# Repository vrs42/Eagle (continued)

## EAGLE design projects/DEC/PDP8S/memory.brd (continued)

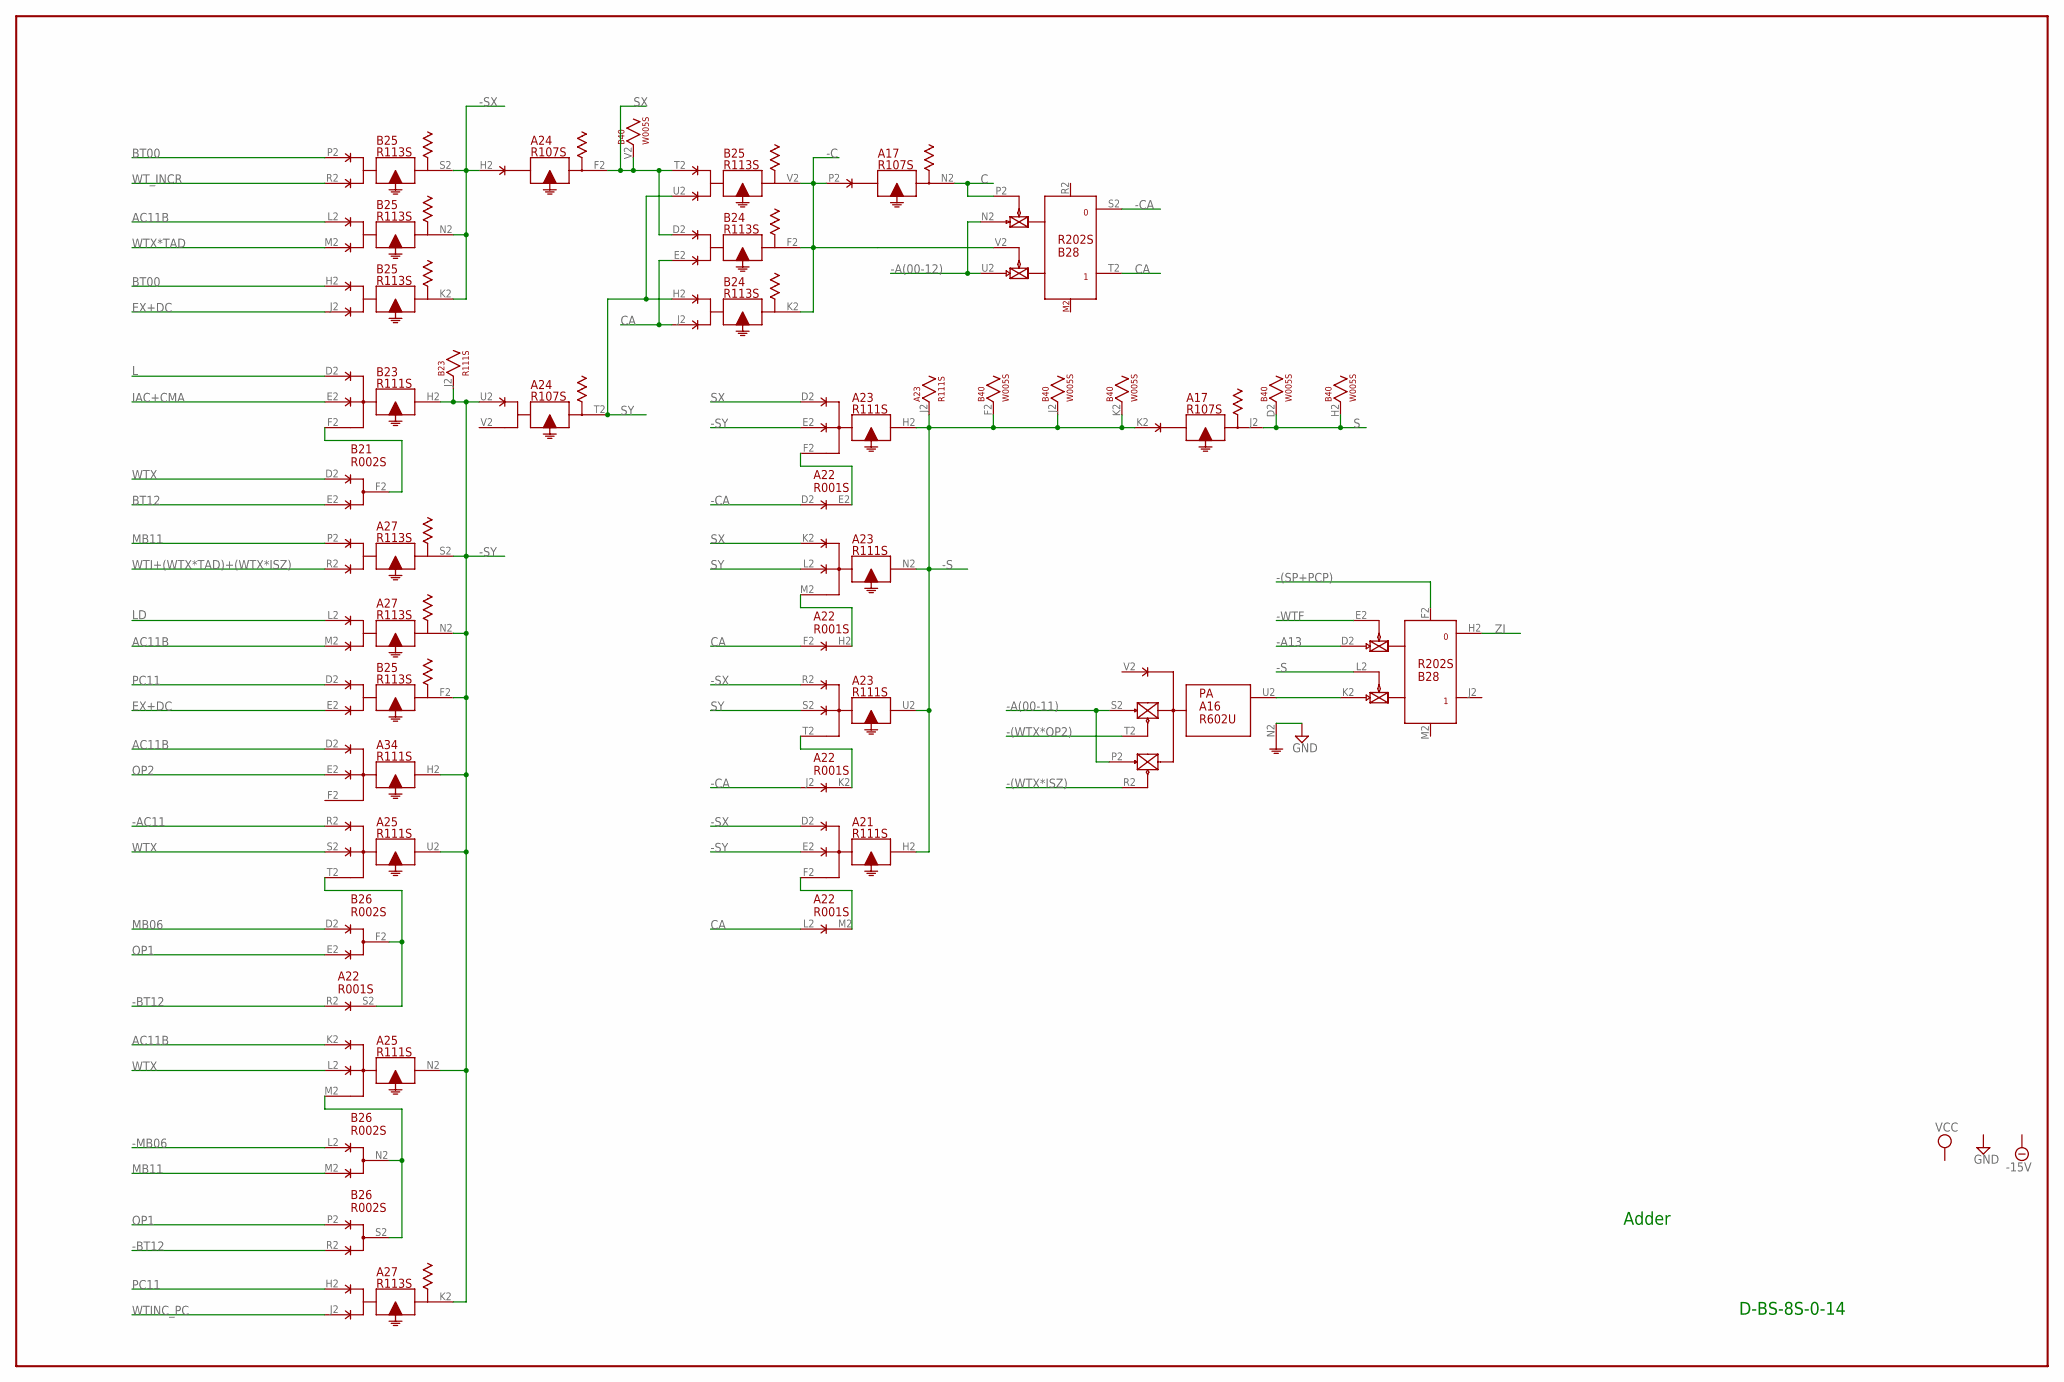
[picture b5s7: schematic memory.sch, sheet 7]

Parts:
A16: R602U; H807S
A17, A24: R107S; H807S
A21, A23, A25, A34: R111S; H807S
A22: R001S; H807S
A27: R113S; H807S
B21, B26: R002S; H807S
B23: R111S; H807S
B24, B25: R113S; H807S
B28: R202S; H807S
B40: W005S; H807S

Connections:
-15V: A16.B2 (-15V), A17.B2 (-15V), A21.B2 (-15V), A22.B2 (-15V), A23.B2 (-15V), A24.B2 (-15V), A25.B2 (-15V), A27.B2 (-15V), A34.B2 (-15V), B21.B2 (-15V), B23.B2 (-15V), B24.B2 (-15V), B25.B2 (-15V), B26.B2 (-15V), B28.B2 (-15V), B40.B2 (-15V); also elsewhere on the board
-(SP+PCP): B28.F2 (RESET); also elsewhere on the board
-(WTX*ISZ): A16.R2 (F); also elsewhere on the board
-(WTX*OP2): A16.T2 (J); also elsewhere on the board
-A13: B28.D2 (PU0); also elsewhere on the board
-A(00-11): A16.P2 (E), A16.S2 (H); also elsewhere on the board
-A(00-12): B28.N2 (PU0), B28.U2 (PU1); also elsewhere on the board
-AC11: A25.R2; also elsewhere on the board
-BT12: A22.R2 (D), B26.R2 (E); also elsewhere on the board
-C: A17.P2, B24.F2, B24.K2, B25.V2, B28.V2 (EN1)
-CA: A22.D2 (D), A22.J2 (D), B28.S2 (0)
-MB06: B26.L2 (D); also elsewhere on the board
-S: A17.K2, A21.H2, A23.H2, A23.J2, A23.N2, A23.U2, B28.L2 (EN1), B40.F2, B40.J2, B40.K2
-SX: A21.D2, A23.R2, A24.H2, B25.K2, B25.N2, B25.S2
-SY: A21.E2, A23.E2, A24.U2, A25.N2, A25.U2, A27.K2, A27.N2, A27.S2, A34.H2, B23.H2, B23.J2, B25.F2
-WTF: B28.E2 (EN0); also elsewhere on the board
AC11B: A25.K2, A27.M2, A34.D2, B25.L2; also elsewhere on the board
BT00: B25.H2, B25.P2; also elsewhere on the board
BT12: B21.E2 (E); also elsewhere on the board
C: A17.N2, B28.P2 (EN0)
CA: A22.F2 (D), A22.L2 (D), B24.E2, B24.J2, B28.T2 (1)
EX+DC: B25.E2, B25.J2; also elsewhere on the board
GND: A16.N2 (C), A17.C2 (GND), A21.C2 (GND), A22.C2 (GND), A23.C2 (GND), A24.C2 (GND), A25.C2 (GND), A27.C2 (GND), A34.C2 (GND), B21.C2 (GND), B23.C2 (GND), B24.C2 (GND), B25.C2 (GND), B26.C2 (GND), B28.C2 (GND), B40.C2 (GND); also elsewhere on the board
IAC+CMA: B23.E2; also elsewhere on the board
L: B23.D2; also elsewhere on the board
LD: A27.L2; also elsewhere on the board
MB06: B26.D2 (D); also elsewhere on the board
MB11: A27.P2, B26.M2 (E); also elsewhere on the board
unnamed: B21.F2 (F), B23.F2
unnamed: A16.U2 (K), B28.K2 (PU1)
unnamed: A22.S2 (E), A25.T2, B26.F2 (F)
unnamed: A22.E2 (E), A23.F2
unnamed: A25.M2, B26.N2 (F), B26.S2 (F)
unnamed: A22.H2 (E), A23.M2
unnamed: A22.K2 (E), A23.T2
unnamed: A21.F2, A22.M2 (E)
OP1: B26.E2 (E), B26.P2 (D); also elsewhere on the board
OP2: A34.E2; also elsewhere on the board
PC11: A27.H2, B25.D2; also elsewhere on the board
S: A17.J2, B40.D2, B40.H2; also elsewhere on the board
SX: A23.D2, A23.K2, A24.F2, B24.D2, B25.T2, B40.V2
SY: A23.L2, A23.S2, A24.T2, B24.H2, B25.U2
VCC: A16.A2 (VCC), A17.A2 (VCC), A21.A2 (VCC), A22.A2 (VCC), A23.A2 (VCC), A24.A2 (VCC), A25.A2 (VCC), A27.A2 (VCC), A34.A2 (VCC), B21.A2 (VCC), B23.A2 (VCC), B24.A2 (VCC), B25.A2 (VCC), B26.A2 (VCC), B28.A2 (VCC), B40.A2 (VCC); also elsewhere on the board
WTI+(WTX*TAD)+(WTX*ISZ): A27.R2; also elsewhere on the board
WTINC_PC: A27.J2; also elsewhere on the board
WTX: A25.L2, A25.S2, B21.D2 (D); also elsewhere on the board
WTX*TAD: B25.M2; also elsewhere on the board
WT_INCR: B25.R2; also elsewhere on the board
ZI: B28.H2 (0); also elsewhere on the board

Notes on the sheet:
D-BS-8S-0-14
Adder

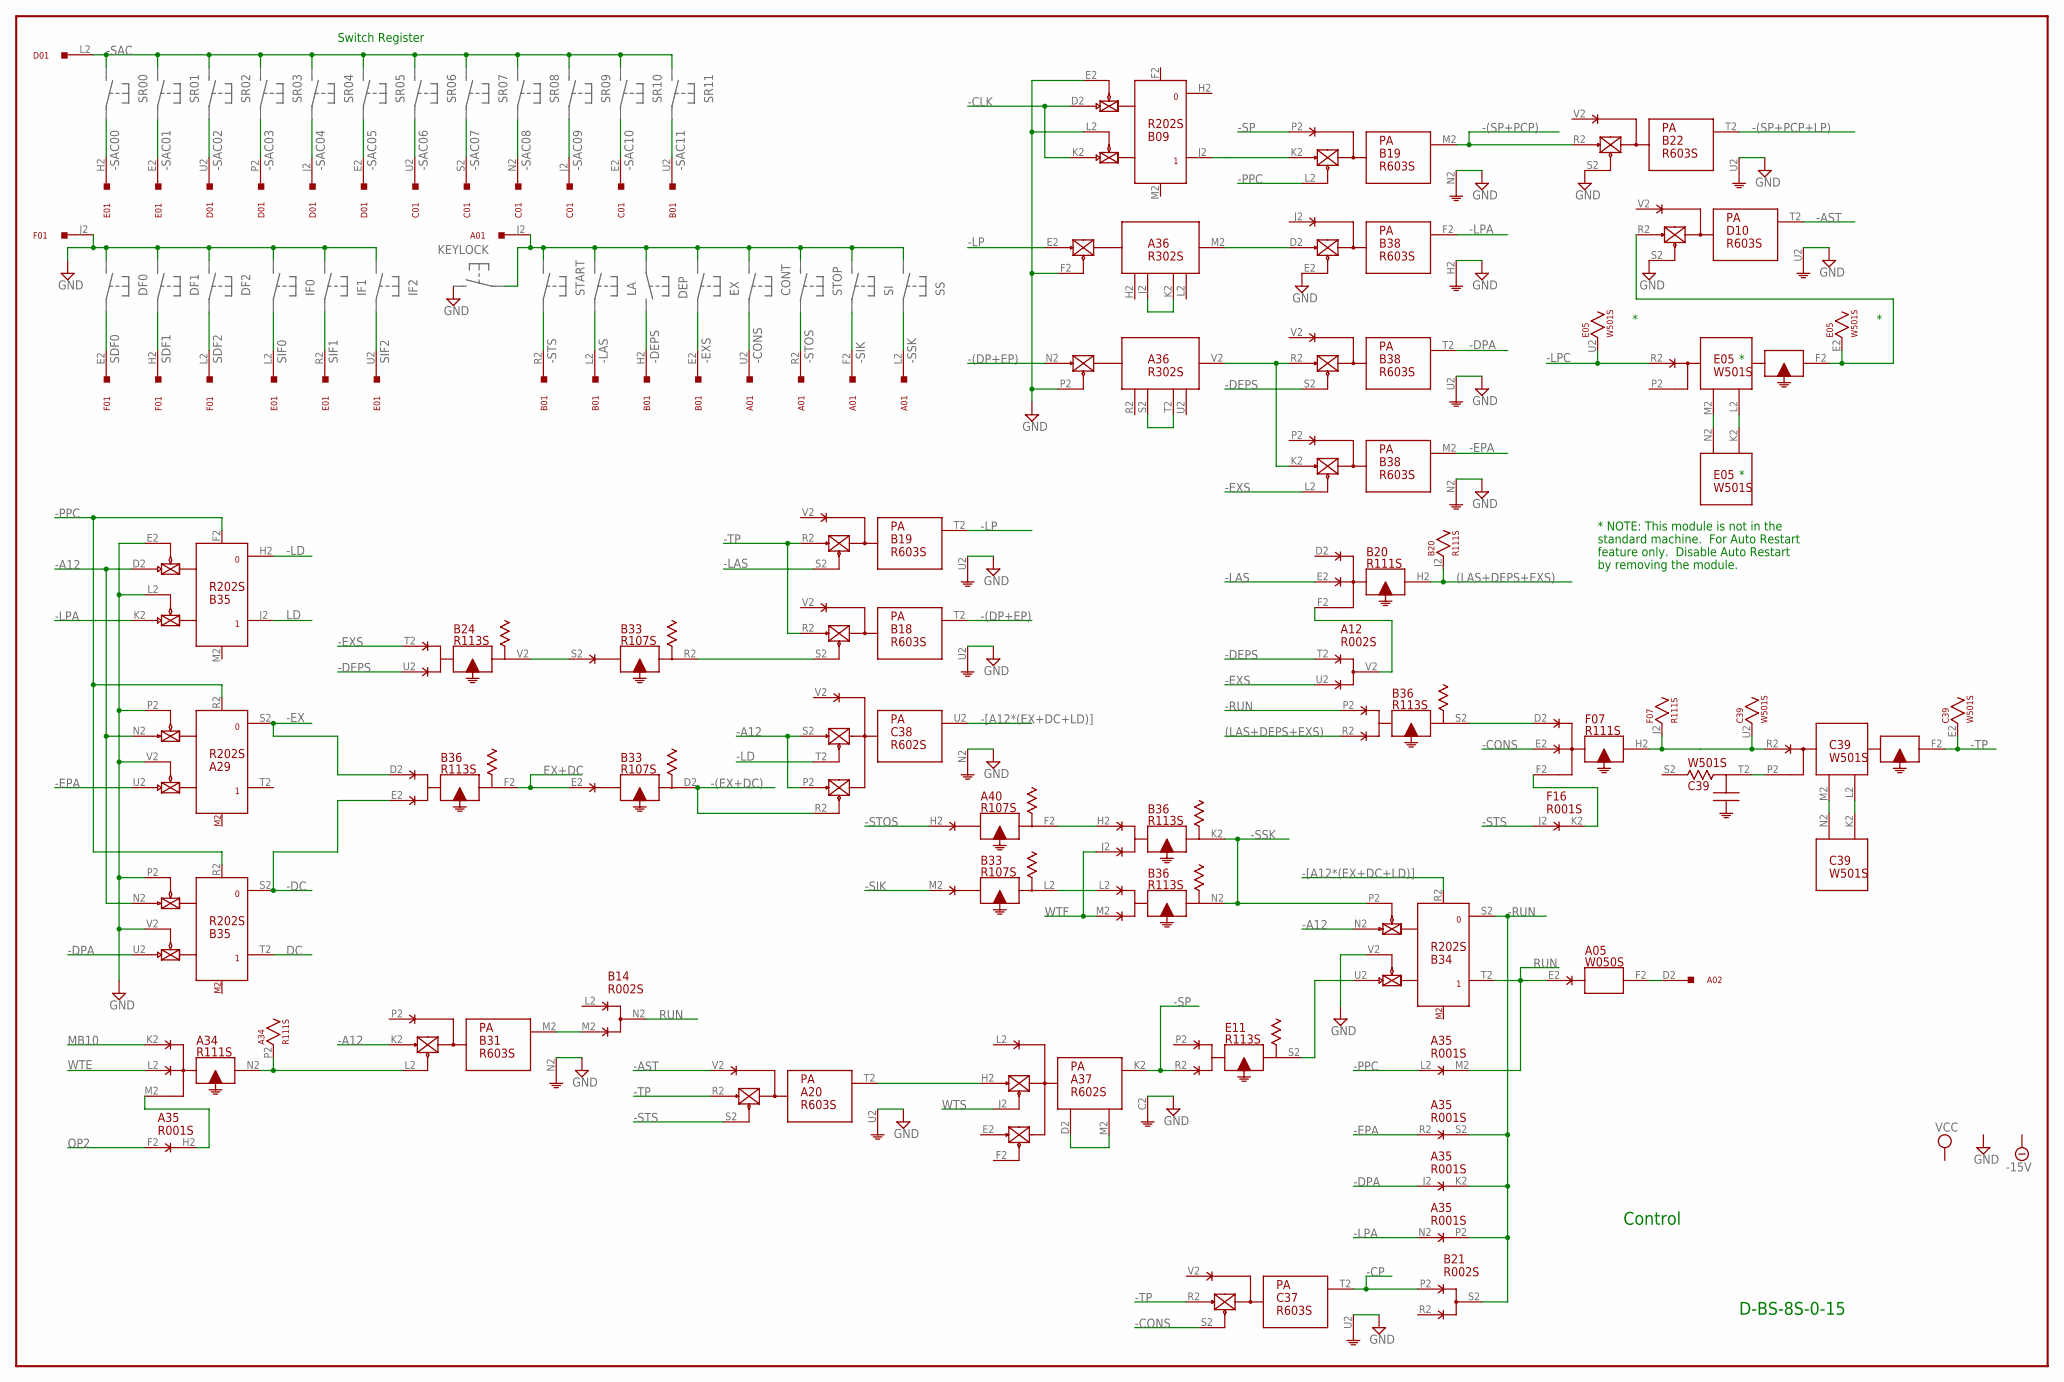
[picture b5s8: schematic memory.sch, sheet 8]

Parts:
A01, A02: W023S; H807S
A05: W050S; H807S
A12: R002S; H807S
A20: R603S; H807S
A29: R202S; H807S
A34: R111S; H807S
A35: R001S; H807S
A36: R302S; H807S
A37: R602S; H807S
A40: R107S; H807S
B01: W023S; H807S
B09, B34, B35: R202S; H807S
B14, B21: R002S; H807S
B18, B19, B22, B31, B38: R603S; H807S
B20: R111S; H807S
B24, B36: R113S; H807S
B33: R107S; H807S
C01: W023S; H807S
C37: R603S; H807S
C38: R602S; H807S
C39: W501S; H807S
D01: W023S; H807S
D10: R603S; H807S
E01: W023S; H807S
E05: W501S; H807S
E11: R113S; H807S
F01: W023S; H807S
F07: R111S; H807S
F16: R001S; H807S

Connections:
(LAS+DEPS+EXS): B20.H2, B20.J2, B36.R2
-15V: A05.B2 (-15V), A12.B2 (-15V), A20.B2 (-15V), A29.B2 (-15V), A34.B2 (-15V), A35.B2 (-15V), A36.B2 (-15V), A37.B2 (-15V), A40.B2 (-15V), B09.B2 (-15V), B14.B2 (-15V), B18.B2 (-15V), B19.B2 (-15V), B20.B2 (-15V), B21.B2 (-15V), B22.B2 (-15V), B24.B2 (-15V), B31.B2 (-15V), B33.B2 (-15V), B34.B2 (-15V), B35.B2 (-15V), B36.B2 (-15V), B38.B2 (-15V), C37.B2 (-15V), C38.B2 (-15V), C39.B2 (-15V), D10.B2 (-15V), E05.B2 (-15V), E11.B2 (-15V), F07.B2 (-15V), F16.B2 (-15V); also elsewhere on the board
-(DP+EP): A36.N2 (E), B18.T2 (O); also elsewhere on the board
-(EX+DC): B33.D2, C38.R2 (F); also elsewhere on the board
-(SP+PCP): B19.M2 (O), B22.R2 (PU0); also elsewhere on the board
-(SP+PCP+LP): B22.T2 (O); also elsewhere on the board
-A12: A29.N2 (PU0), B31.K2 (PU0), B34.N2 (PU0), B35.D2 (PU0), B35.N2 (PU0), C38.P2 (E), C38.S2 (H); also elsewhere on the board
-AST: A20.V2, D10.T2 (O)
-CLK: B09.D2 (PU0), B09.K2 (PU1); also elsewhere on the board
-CONS: A01.U2, C37.S2 (EN0), F07.E2
-CP: B21.P2 (D), C37.T2 (O)
-DC: B35.S2 (0), B36.E2; also elsewhere on the board
-DEPS: A12.T2 (D), B01.H2, B24.U2, B38.S2 (EN0)
-DPA: A35.J2 (D), B35.U2 (PU1), B38.T2 (O); also elsewhere on the board
-EPA: A29.U2 (PU1), A35.R2 (D), B38.M2 (O); also elsewhere on the board
-EX: A29.S2 (0), B36.D2; also elsewhere on the board
-EXS: A12.U2 (E), B01.E2, B24.T2, B38.L2 (EN0)
-LAS: B01.L2, B19.S2 (EN0), B20.E2
-LD: B35.H2 (0), C38.T2 (J); also elsewhere on the board
-LP: A36.E2 (E), B19.T2 (O); also elsewhere on the board
-LPA: A35.N2 (D), B35.K2 (PU1), B38.F2 (O); also elsewhere on the board
-LPC: E05.R2 (R), E05.U2; also elsewhere on the board
-PPC: A29.R2 (RESET), A35.L2 (D), B19.L2 (EN0), B35.F2 (RESET), B35.R2 (RESET); also elsewhere on the board
-RUN: A35.K2 (E), A35.P2 (E), A35.S2 (E), B21.S2 (F), B34.S2 (0), B36.P2; also elsewhere on the board
-SAC: D01.L2; also elsewhere on the board
-SAC00: E01.H2; also elsewhere on the board
-SAC01: E01.E2; also elsewhere on the board
-SAC02: D01.U2; also elsewhere on the board
-SAC03: D01.P2; also elsewhere on the board
-SAC04: D01.J2; also elsewhere on the board
-SAC05: D01.E2; also elsewhere on the board
-SAC06: C01.U2; also elsewhere on the board
-SAC07: C01.S2; also elsewhere on the board
-SAC08: C01.N2; also elsewhere on the board
-SAC09: C01.J2; also elsewhere on the board
-SAC10: C01.E2; also elsewhere on the board
-SAC11: B01.U2; also elsewhere on the board
-SIK: A01.F2, B33.M2
-SP: A37.K2 (K), B19.P2, E11.R2; also elsewhere on the board
-SSK: A01.L2, B34.P2 (EN0), B36.K2, B36.N2
-STOS: A01.R2, A40.H2
-STS: A20.S2 (EN0), B01.R2, F16.J2 (D)
-TP: A20.R2 (PU0), B18.R2 (PU0), B19.R2 (PU0), C37.R2 (PU0), C39.E2, C39.F2 (F)
-[A12*(EX+DC+LD)]: B34.R2 (RESET), C38.U2 (K); also elsewhere on the board
DC: B35.T2 (1); also elsewhere on the board
EX+DC: B33.E2, B36.F2; also elsewhere on the board
GND: A05.C2 (GND), A12.C2 (GND), A20.C2 (GND), A20.U2 (G), A29.C2 (GND), A29.P2 (EN0), A29.V2 (EN1), A34.C2 (GND), A35.C2 (GND), A36.C2 (GND), A36.F2 (F), A36.P2 (F), A37.C2 (GND), A40.C2 (GND), B09.C2 (GND), B09.E2 (EN0), B09.L2 (EN1), B14.C2 (GND), B18.C2 (GND), B18.U2 (G), B19.C2 (GND), B19.N2 (G), B19.U2 (G), B20.C2 (GND), B21.C2 (GND), B22.C2 (GND), B22.S2 (EN0), B22.U2 (G), B24.C2 (GND), B31.C2 (GND), B31.N2 (G), B33.C2 (GND), B34.C2 (GND), B34.V2 (EN1), B35.C2 (GND), B35.E2 (EN0), B35.L2 (EN1), B35.P2 (EN0), B35.V2 (EN1), B36.C2 (GND), B38.C2 (GND), B38.E2 (EN0), B38.H2 (G), B38.N2 (G), B38.U2 (G), C37.C2 (GND), C37.U2 (G), C38.N2 (C), C39.C2 (GND), C39.V2 (GND), D10.C2 (GND), D10.S2 (EN0), D10.U2 (G), E05.C2 (GND), E05.V2 (GND), E11.C2 (GND), F01.J2, F07.C2 (GND), F16.C2 (GND); also elsewhere on the board
KEYLOCK: A01.J2
LD: B35.J2 (1); also elsewhere on the board
MB10: A34.K2; also elsewhere on the board
unnamed: A34.M2, A35.H2 (E)
unnamed: A34.N2, A34.P2, B31.L2 (EN0)
unnamed: B14.M2 (E), B31.M2 (O)
unnamed: B24.V2, B33.S2
unnamed: B34.U2 (PU1), E11.S2
unnamed: B18.S2 (EN0), B33.R2
unnamed: A36.S2 (J), A36.T2 (K)
unnamed: A36.J2 (J), A36.K2 (K)
unnamed: E05.M2 (M), E05.N2 (N)
unnamed: E05.K2 (K), E05.L2 (L)
unnamed: B09.J2 (1), B19.K2 (PU0)
unnamed: D10.R2 (PU0), E05.E2, E05.F2 (F)
unnamed: A36.M2 (M), B38.D2 (PU0)
unnamed: A36.V2 (M), B38.K2 (PU0), B38.R2 (PU0)
unnamed: A12.V2 (F), B20.F2
unnamed: C39.M2 (M), C39.N2 (N)
unnamed: C39.K2 (K), C39.L2 (L)
unnamed: C39.P2, C39.T2 (T)
unnamed: C39.R2 (R), C39.U2, F07.H2, F07.J2
unnamed: B36.S2, F07.D2
unnamed: F07.F2, F16.K2 (E)
unnamed: A02.D2, A05.F2
unnamed: B33.L2, B36.L2
unnamed: A40.F2, B36.H2
unnamed: A37.D2 (D), A37.M2 (M)
unnamed: A20.T2 (O), A37.H2 (H)
OP2: A35.F2 (D); also elsewhere on the board
RUN: A05.E2, A35.M2 (E), B14.N2 (F), B34.T2 (1)
SDF0: F01.E2; also elsewhere on the board
SDF1: F01.H2; also elsewhere on the board
SDF2: F01.L2; also elsewhere on the board
SIF0: E01.L2; also elsewhere on the board
SIF1: E01.R2; also elsewhere on the board
SIF2: E01.U2; also elsewhere on the board
VCC: A05.A2 (VCC), A12.A2 (VCC), A20.A2 (VCC), A29.A2 (VCC), A34.A2 (VCC), A35.A2 (VCC), A36.A2 (VCC), A37.A2 (VCC), A40.A2 (VCC), B09.A2 (VCC), B14.A2 (VCC), B18.A2 (VCC), B19.A2 (VCC), B20.A2 (VCC), B21.A2 (VCC), B22.A2 (VCC), B24.A2 (VCC), B31.A2 (VCC), B33.A2 (VCC), B34.A2 (VCC), B35.A2 (VCC), B36.A2 (VCC), B38.A2 (VCC), C37.A2 (VCC), C38.A2 (VCC), C39.A2 (VCC), D10.A2 (VCC), E05.A2 (VCC), E11.A2 (VCC), F07.A2 (VCC), F16.A2 (VCC); also elsewhere on the board
WTE: A34.L2; also elsewhere on the board
WTF: B36.J2, B36.M2; also elsewhere on the board
WTS: A37.J2 (J); also elsewhere on the board

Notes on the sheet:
D-BS-8S-0-15
Control
Switch Register
* NOTE: This module is not in the
standard machine. For Auto Restart
feature only. Disable Auto Restart
by removing the module.

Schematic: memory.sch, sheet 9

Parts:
A02: W023S; H807S
A06, A07: W050S; H807S
A18: R107S; H807S
B02: W023S; H807S
B13, B20: R111S; H807S
B21: R002S; H807S
B22: R603S; H807S
C11: R001S; H807S
C37: R603S; H807S
D17: R151S; H807S
D19, D20: R202S; H807S
E09, E10, E11, E13: R113S; H807S
F13, F18, F19, F20: R107S; H807S
F14: R113S; H807S
F15, F17: R111S; H807S
F16: R001S; H807S

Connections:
(ISZ*ZI)+JMS+(OP+IOT)*SKP: F15.N2, F15.P2, F19.M2; also elsewhere on the board
-15V: A06.B2 (-15V), A07.B2 (-15V), A18.B2 (-15V), B13.B2 (-15V), B20.B2 (-15V), B21.B2 (-15V), B22.B2 (-15V), C11.B2 (-15V), C37.B2 (-15V), D17.B2 (-15V), D19.B2 (-15V), D20.B2 (-15V), E09.B2 (-15V), E10.B2 (-15V), E11.B2 (-15V), E13.B2 (-15V), F13.B2 (-15V), F14.B2 (-15V), F15.B2 (-15V), F16.B2 (-15V), F17.B2 (-15V), F18.B2 (-15V), F19.B2 (-15V), F20.B2 (-15V); also elsewhere on the board
-(IAC+CMA): B21.H2 (D), E10.R2, F19.T2
-(ISZ*Z1): E11.V2, F16.N2 (D)
-(OP+IOT): E11.M2, F13.R2; also elsewhere on the board
-(SP+PCP+LP): C37.P2; also elsewhere on the board
-A00: C37.K2 (PU0); also elsewhere on the board
-A1: E09.T2; also elsewhere on the board
-A(00-11): B22.K2 (PU0); also elsewhere on the board
-AND: B13.K2, B20.K2, D17.M2 (M), F15.R2, F20.E2
-CLL: E13.S2, F19.P2; also elsewhere on the board
-CMA: F14.K2, F14.M2
-CML: E13.V2, F13.E2; also elsewhere on the board
-DCA: B20.S2, B21.M2 (E), D17.R2 (R), F20.M2
-IAC: F14.F2, F14.L2
-IOT: D17.U2 (U), E11.J2, F20.U2
-IR00: D17.J2 (J), D20.H2 (0), D20.V2 (EN1)
-IR01: D17.E2 (E), D19.L2 (EN1), D20.S2 (0)
-IR02: D17.K2 (K), D19.H2 (0), D19.V2 (EN1)
-IR03: A18.U2, D19.S2 (0), E10.E2; also elsewhere on the board
-IRCLR: C37.M2 (O), D19.F2 (RESET), D19.R2 (RESET), D20.F2 (RESET), D20.R2 (RESET); also elsewhere on the board
-IRSH: B22.M2 (O), D19.D2 (PU0), D19.K2 (PU1), D19.N2 (PU0), D19.U2 (PU1), D20.D2 (PU0), D20.K2 (PU1), D20.N2 (PU0), D20.U2 (PU1)
-ISZ: B21.U2 (E), C11.T2 (D), D17.P2, F20.K2
-JMP: D17.T2 (T), E10.M2, F16.R2 (D), F20.S2; also elsewhere on the board
-JMS: B20.R2, D17.S2 (S), F15.L2, F20.P2; also elsewhere on the board
-MB10: E09.D2; also elsewhere on the board
-MB11: D20.L2 (EN1); also elsewhere on the board
-OP1: E10.F2, F16.T2 (D), F18.K2
-OP2: B21.J2 (E), B21.T2 (D), E09.M2, E11.F2, F18.P2
-OPR: D17.V2 (V), E11.H2, F19.K2; also elsewhere on the board
-ROTL: B21.L2 (D), F17.N2, F17.P2, F17.S2
-ROTR: F17.H2, F17.J2, F17.R2, F19.S2; also elsewhere on the board
-TAD: B13.L2, B20.L2, D17.N2 (N), E10.P2, F15.S2, F16.L2 (D), F20.H2; also elsewhere on the board
-WTB: C37.L2 (EN0); also elsewhere on the board
-WTF: B22.L2 (EN0); also elsewhere on the board
-[(ISZ*ZI)+JMS+(OP+IOT)*SKP+JMP]: F19.F2; also elsewhere on the board
A1: E09.P2; also elsewhere on the board
AND: A06.H2, F20.D2; also elsewhere on the board
AND+TAD+DCA+IAC+CMA+ROTL+OP2: B20.N2, B20.P2; also elsewhere on the board
AND+TAD+ISZ: B13.N2, B13.P2; also elsewhere on the board
AND+TAD+OP1+JMP: F15.U2, F15.V2; also elsewhere on the board
BT00: E09.E2, E09.H2; also elsewhere on the board
CLL: F19.N2; also elsewhere on the board
CML: F13.D2; also elsewhere on the board
DCA: A06.P2, F20.L2; also elsewhere on the board
EX+DC: D17.D2 (D); also elsewhere on the board
GND: A06.C2 (GND), A07.C2 (GND), A18.C2 (GND), B13.C2 (GND), B20.C2 (GND), B21.C2 (GND), B22.C2 (GND), B22.N2 (G), C11.C2 (GND), C37.C2 (GND), C37.N2 (G), D17.C2 (GND), D19.C2 (GND), D20.C2 (GND), E09.C2 (GND), E10.C2 (GND), E11.C2 (GND), E13.C2 (GND), F13.C2 (GND), F14.C2 (GND), F15.C2 (GND), F16.C2 (GND), F17.C2 (GND), F18.C2 (GND), F19.C2 (GND), F20.C2 (GND); also elsewhere on the board
IAC+CMA: F14.N2, F19.U2; also elsewhere on the board
IOT: A07.E2, F20.T2; also elsewhere on the board
IR00: D17.H2 (H), D20.J2 (1), D20.P2 (EN0)
IR01: D17.F2 (F), D19.E2 (EN0), D20.T2 (1)
IR02: D17.L2 (L), D19.J2 (1), D19.P2 (EN0)
IR03: D19.T2 (1), E11.D2; also elsewhere on the board
IR03*-A1: F13.J2; also elsewhere on the board
IR03*A1: F13.N2; also elsewhere on the board
IR03B: A18.T2, E09.R2, E09.U2
ISZ: A06.M2, E11.T2, F20.J2
ISZ+DCA+JMS: F18.T2; also elsewhere on the board
JMP: A06.U2, F20.R2; also elsewhere on the board
JMS: A06.S2, F20.N2; also elsewhere on the board
JMS+DCA+ISZ+OP2: B20.U2, B20.V2, E09.L2
MB05: E13.P2; also elsewhere on the board
MB06: F14.J2; also elsewhere on the board
MB07: E13.T2; also elsewhere on the board
MB08: F17.E2; also elsewhere on the board
MB09: F17.L2; also elsewhere on the board
MB10: E09.J2; also elsewhere on the board
MB11: D20.E2 (EN0), F14.E2; also elsewhere on the board
unnamed: A02.V2, A07.F2
unnamed: A02.N2, A06.J2
unnamed: F15.T2, F16.S2 (E), F16.U2 (E)
unnamed: B20.M2, B21.K2 (F), B21.N2 (F)
unnamed: B13.M2, C11.U2 (E)
unnamed: A02.P2, A06.L2
unnamed: E09.S2, F13.P2
unnamed: F16.M2 (E), F17.T2
unnamed: E09.V2, F13.K2
unnamed: A02.R2, A06.N2
unnamed: F16.E2 (E), F17.F2
unnamed: F16.H2 (E), F17.M2
unnamed: A02.U2, A06.V2
unnamed: E09.F2, F16.D2 (D)
unnamed: E09.K2, F16.F2 (D)
unnamed: E10.L2, F19.L2
unnamed: A07.J2, B02.D2
unnamed: E11.N2, F15.K2
unnamed: E10.N2, F19.H2
unnamed: B20.T2, B21.V2 (F)
unnamed: A02.T2, A06.T2
unnamed: F15.M2, F16.P2 (E)
unnamed: A02.S2, A06.R2
unnamed: E09.N2, F18.U2
OP1: E13.R2, E13.U2, F14.D2, F14.H2, F17.D2, F17.K2, F18.J2; also elsewhere on the board
OP2: F18.N2; also elsewhere on the board
OP+IOT: E11.K2, F13.S2
OPR: A07.H2, E10.D2, E11.E2, F19.J2
ROTR: F19.R2; also elsewhere on the board
ROTR+ROTL+TAD: F17.U2, F17.V2; also elsewhere on the board
SKP: E11.L2; also elsewhere on the board
TAD: A06.K2, F20.F2; also elsewhere on the board
TAD+IAC+CMA: E10.S2; also elsewhere on the board
VCC: A06.A2 (VCC), A07.A2 (VCC), A18.A2 (VCC), B13.A2 (VCC), B20.A2 (VCC), B21.A2 (VCC), B22.A2 (VCC), C11.A2 (VCC), C37.A2 (VCC), D17.A2 (VCC), D19.A2 (VCC), D20.A2 (VCC), E09.A2 (VCC), E10.A2 (VCC), E11.A2 (VCC), E13.A2 (VCC), F13.A2 (VCC), F14.A2 (VCC), F15.A2 (VCC), F16.A2 (VCC), F17.A2 (VCC), F18.A2 (VCC), F19.A2 (VCC), F20.A2 (VCC); also elsewhere on the board
ZI: E11.U2; also elsewhere on the board

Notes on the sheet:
D-BS-8S-0-16
Instruction Register

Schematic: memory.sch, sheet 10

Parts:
A08, A27: R113S; H807S
A09, A17, A24, A40: R107S; H807S
A11, A25, A38: R111S; H807S
A35: R001S; H807S
A39: R002S; H807S
B36: R113S; H807S
B37: R107S; H807S
B39: W028S; H807S
B40: W005S; H807S
C11: R001S; H807S
C38: R602S; H807S
C40: W506S; H807S
D06: R113S; H807S
D36: R111S; H807S
D37: R302S; H807S
D38: R202S; H807S
D39: R002S; H807S
E07: W050S; H807S
E10: R113S; H807S
E37: W028S; H807S
F02: W023S; H807S
F06: R001S; H807S
F07, F15, F40: R111S; H807S
F18, F19: R107S; H807S
F22: W005S; H807S
F23: R202S; H807S
F36: R113S; H807S
F37, F38, F39: R602S; H807S

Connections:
-15V: A08.B2 (-15V), A09.B2 (-15V), A11.B2 (-15V), A17.B2 (-15V), A24.B2 (-15V), A25.B2 (-15V), A27.B2 (-15V), A35.B2 (-15V), A38.B2 (-15V), A39.B2 (-15V), A40.B2 (-15V), B36.B2 (-15V), B37.B2 (-15V), B40.B2 (-15V), C11.B2 (-15V), C38.B2 (-15V), C40.B2 (-15V), D06.B2 (-15V), D36.B2 (-15V), D37.B2 (-15V), D38.B2 (-15V), D39.B2 (-15V), E07.B2 (-15V), E10.B2 (-15V), F06.B2 (-15V), F07.B2 (-15V), F15.B2 (-15V), F18.B2 (-15V), F19.B2 (-15V), F22.B2 (-15V), F23.B2 (-15V), F36.B2 (-15V), F37.B2 (-15V), F38.B2 (-15V), F39.B2 (-15V), F40.B2 (-15V); also elsewhere on the board
-(SP+PCP): A17.M2, E10.H2, F18.S2, F19.E2; also elsewhere on the board
-A00: C38.H2 (H), D38.K2 (PU1); also elsewhere on the board
-A12: F23.K2 (PU1); also elsewhere on the board
-A13: F23.D2 (PU0); also elsewhere on the board
-CAC: F15.H2; also elsewhere on the board
-FR: A35.D2 (D); also elsewhere on the board
-INT_REQ: A24.R2, A40.E2, B40.E2, B40.N2, D36.V2, E37.M2, F36.K2
-IOP1: A40.K2, A40.S2, A40.U2, D38.U2 (PU1), F36.L2, F37.K2 (K)
-IOP2: A08.P2, A08.T2, A11.D2, A40.M2, D38.D2 (PU0), D38.N2 (PU0), F38.K2 (K); also elsewhere on the board
-IOP4: A27.T2, A38.K2, B36.T2, B37.E2, F39.K2 (K); also elsewhere on the board
-IO_SKP: A09.K2, B40.M2, B40.P2, D36.U2, E37.K2, F07.N2
-IO_SKS: A11.N2, A11.P2; also elsewhere on the board
-IRCLR: D38.F2 (RESET), D38.R2 (RESET); also elsewhere on the board
-LPC: A40.P2, C40.M2 (M); also elsewhere on the board
-MB03: A38.D2, F40.D2; also elsewhere on the board
-MB04: A38.E2, F40.E2; also elsewhere on the board
-MB05: D39.D2 (D); also elsewhere on the board
-MB06: A39.J2 (E), D39.E2 (E); also elsewhere on the board
-MB07: A39.D2 (D), D39.H2 (D); also elsewhere on the board
-MB08: A39.E2 (E), D39.J2 (E); also elsewhere on the board
-MB09: F39.J2 (J); also elsewhere on the board
-MB10: F38.J2 (J); also elsewhere on the board
-MB11: F37.J2 (J); also elsewhere on the board
-MPC: C40.K2 (K); also elsewhere on the board
-PE: F06.R2 (D); also elsewhere on the board
-PE_SEL: A24.P2, A38.H2, A38.J2; also elsewhere on the board
-PIR: F23.H2 (0); also elsewhere on the board
-PISEL: D38.E2 (EN0), D38.P2 (EN0), D38.V2 (EN1), F40.H2, F40.J2
-PPC: C40.L2 (L); also elsewhere on the board
-RUN: F36.R2; also elsewhere on the board
B_RUN: E37.S2, F36.S2
CLR_AC: D06.T2, E37.P2, F22.U2
GND: A08.C2 (GND), A09.C2 (GND), A11.C2 (GND), A17.C2 (GND), A24.C2 (GND), A25.C2 (GND), A27.C2 (GND), A35.C2 (GND), A38.C2 (GND), A39.C2 (GND), A40.C2 (GND), B36.C2 (GND), B37.C2 (GND), B39.C2 (GND), B39.F2 (GND), B39.J2 (GND), B39.L2 (GND), B39.N2 (GND), B39.R2 (GND), B39.U2 (GND), B40.C2 (GND), C11.C2 (GND), C38.C2 (GND), C40.C2 (GND), D06.C2 (GND), D36.C2 (GND), D37.C2 (GND), D37.F2 (F), D37.P2 (F), D38.C2 (GND), D39.C2 (GND), E07.C2 (GND), E10.C2 (GND), E37.C2 (GND), E37.F2 (GND), E37.J2 (GND), E37.L2 (GND), E37.N2 (GND), E37.R2 (GND), E37.U2 (GND), F06.C2 (GND), F07.C2 (GND), F15.C2 (GND), F18.C2 (GND), F19.C2 (GND), F22.C2 (GND), F23.C2 (GND), F23.E2 (EN0), F36.C2 (GND), F37.C2 (GND), F38.C2 (GND), F39.C2 (GND), F40.C2 (GND); also elsewhere on the board
INS: A25.D2, D38.T2 (1)
ION: D38.J2 (1), E07.M2, F40.L2
IOP1: A40.J2, A40.R2, A40.T2, B39.K2, B40.U2, F07.K2, F36.N2
IOP2: A08.S2, A08.V2, A11.H2, A11.J2, A40.L2, B39.M2, B40.T2, D36.S2
IOP4: A27.V2, A38.N2, A38.P2, B36.V2, B37.D2, B39.P2, B40.S2
IOT: A11.L2, F40.R2; also elsewhere on the board
IO_CLEAR: A17.L2, B39.V2, E10.K2, F18.R2, F19.D2
IO_INT: A40.D2, F40.K2
MB05: A39.H2 (D); also elsewhere on the board
unnamed: F23.L2 (EN1), F40.N2, F40.P2
unnamed: D06.V2, F15.D2
unnamed: A35.E2 (E), F40.M2
unnamed: F38.D2 (D), F38.M2 (M)
unnamed: A09.J2, A11.K2
unnamed: A25.H2, A25.J2, D38.L2 (EN1)
unnamed: E07.N2, F02.V2
unnamed: F37.D2 (D), F37.M2 (M)
unnamed: D39.F2 (F), D39.K2 (F), F40.F2
unnamed: C40.F2 (F), C40.H2 (H)
unnamed: C38.F2 (F), C38.J2 (J), F40.U2, F40.V2
unnamed: D37.J2 (J), D37.K2 (K)
unnamed: D37.S2 (J), D37.T2 (K)
unnamed: F06.S2 (E), F07.M2
unnamed: C11.H2 (E), D36.T2
unnamed: A38.F2, A39.F2 (F), A39.K2 (F)
unnamed: A40.N2, D36.R2, F36.H2
PE: A24.S2; also elsewhere on the board
PE_SEL: A24.N2, C11.F2 (D), F07.L2
PIR: F23.J2 (1); also elsewhere on the board
SP0: C38.K2 (K), D37.E2 (E), F37.H2 (H)
SP1: D37.M2 (M), D37.N2 (E), F38.H2 (H)
SP2: D37.V2 (M), F39.H2 (H)
VCC: A08.A2 (VCC), A09.A2 (VCC), A11.A2 (VCC), A17.A2 (VCC), A24.A2 (VCC), A25.A2 (VCC), A27.A2 (VCC), A35.A2 (VCC), A38.A2 (VCC), A39.A2 (VCC), A40.A2 (VCC), B36.A2 (VCC), B37.A2 (VCC), B40.A2 (VCC), C11.A2 (VCC), C38.A2 (VCC), C40.A2 (VCC), D06.A2 (VCC), D36.A2 (VCC), D37.A2 (VCC), D38.A2 (VCC), D39.A2 (VCC), E07.A2 (VCC), E10.A2 (VCC), F06.A2 (VCC), F07.A2 (VCC), F15.A2 (VCC), F18.A2 (VCC), F19.A2 (VCC), F22.A2 (VCC), F23.A2 (VCC), F36.A2 (VCC), F37.A2 (VCC), F38.A2 (VCC), F39.A2 (VCC), F40.A2 (VCC); also elsewhere on the board
WTF: A25.E2; also elsewhere on the board
WTX: F40.S2; also elsewhere on the board

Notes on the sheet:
D-BS-8S-0-17
In-Out

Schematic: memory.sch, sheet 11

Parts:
A07: W050S; H807S
B02: W023S; H807S
B06: W050S; H807S
B18: R603S; H807S
C06: W050S; H807S
C14: R113S; H807S
C15, C16, C17, C18, C19, C20: R202S; H807S
D03: W050S; H807S
D18: R107S; H807S
E02: W023S; H807S
E07: W050S; H807S
F02: W023S; H807S

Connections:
-15V: A07.B2 (-15V), B06.B2 (-15V), B18.B2 (-15V), C06.B2 (-15V), C14.B2 (-15V), C15.B2 (-15V), C16.B2 (-15V), C17.B2 (-15V), C18.B2 (-15V), C19.B2 (-15V), C20.B2 (-15V), D03.B2 (-15V), D18.B2 (-15V), E07.B2 (-15V); also elsewhere on the board
-A(00-11): B18.D2 (PU0); also elsewhere on the board
-PPC: C15.M2 (SET), C16.M2 (SET), C17.M2 (SET), C18.M2 (SET), C19.M2 (SET), C20.M2 (SET); also elsewhere on the board
-RIPC: C14.F2, C14.K2, C14.N2, C14.S2, C15.E2 (EN0), D18.H2
-[WTF+WTX*(JMP+JMS)+WTE+WTB+EX+DC+LD]: B18.E2 (EN0); also elsewhere on the board
GND: A07.C2 (GND), B06.C2 (GND), B18.C2 (GND), B18.H2 (G), C06.C2 (GND), C14.C2 (GND), C15.C2 (GND), C16.C2 (GND), C17.C2 (GND), C18.C2 (GND), C19.C2 (GND), C20.C2 (GND), D03.C2 (GND), D18.C2 (GND), E07.C2 (GND); also elsewhere on the board
MA11B: C14.D2; also elsewhere on the board
unnamed: C15.H2 (0), C15.V2 (EN1), E07.U2
unnamed: C15.J2 (1), C15.P2 (EN0)
unnamed: B18.F2 (O), C15.D2 (PU0), C15.K2 (PU1), C15.N2 (PU0), C15.U2 (PU1), C16.D2 (PU0), C16.K2 (PU1), C16.N2 (PU0), C16.U2 (PU1), C17.D2 (PU0), C17.K2 (PU1), C17.N2 (PU0), C17.U2 (PU1), C18.D2 (PU0), C18.K2 (PU1), C18.N2 (PU0), C18.U2 (PU1), C19.D2 (PU0), C19.K2 (PU1), C19.N2 (PU0), C19.U2 (PU1), C20.D2 (PU0), C20.K2 (PU1), C20.N2 (PU0), C20.U2 (PU1)
unnamed: C16.H2 (0), C16.V2 (EN1), D03.U2
unnamed: C16.J2 (1), C16.P2 (EN0)
unnamed: A07.L2, B02.E2
unnamed: C06.S2, C17.H2 (0), C17.V2 (EN1)
unnamed: C17.J2 (1), C17.P2 (EN0)
unnamed: A07.N2, B02.F2
unnamed: B06.E2, C18.H2 (0), C18.V2 (EN1)
unnamed: C18.J2 (1), C18.P2 (EN0)
unnamed: A07.V2, B02.K2
unnamed: A07.S2, C19.H2 (0), C19.V2 (EN1)
unnamed: C19.J2 (1), C19.P2 (EN0)
unnamed: A07.T2, B02.J2
unnamed: A07.M2, C20.H2 (0), C20.V2 (EN1)
unnamed: C20.J2 (1), C20.P2 (EN0)
unnamed: A07.R2, B02.H2
unnamed: C15.S2 (0), C16.L2 (EN1), E07.E2
unnamed: C15.T2 (1), C16.E2 (EN0)
unnamed: C06.U2, C16.S2 (0), C17.L2 (EN1)
unnamed: C16.T2 (1), C17.E2 (EN0)
unnamed: B06.H2, C17.S2 (0), C18.L2 (EN1)
unnamed: A07.U2, C18.S2 (0), C19.L2 (EN1)
unnamed: C18.T2 (1), C19.E2 (EN0)
unnamed: C17.T2 (1), C18.E2 (EN0)
unnamed: A07.P2, C19.S2 (0), C20.L2 (EN1)
unnamed: C19.T2 (1), C20.E2 (EN0)
unnamed: B02.M2, B06.J2
unnamed: B02.L2, B06.F2
unnamed: D03.V2, E02.V2
unnamed: C06.V2, E02.U2
unnamed: C06.T2, E02.T2
unnamed: E07.V2, F02.E2
unnamed: E07.F2, F02.D2
PC11: A07.K2, C14.L2, C20.S2 (0); also elsewhere on the board
RIPC: C15.L2 (EN1), D18.F2
S: C14.H2, C14.R2; also elsewhere on the board
VCC: A07.A2 (VCC), B06.A2 (VCC), B18.A2 (VCC), C06.A2 (VCC), C14.A2 (VCC), C15.A2 (VCC), C16.A2 (VCC), C17.A2 (VCC), C18.A2 (VCC), C19.A2 (VCC), C20.A2 (VCC), D03.A2 (VCC), D18.A2 (VCC), E07.A2 (VCC); also elsewhere on the board
WTE*-[(ISZ*ZI)+JMS+(OP+IOT)*SKP+JMP]: C14.M2; also elsewhere on the board
WTE*[(ISZ*ZI)+JMS+(OP+IOT)*SKP]: C14.J2; also elsewhere on the board
WTF+WTB+EX+DC+LD: C14.P2; also elsewhere on the board
WTX*(JMP+JMS): C14.E2; also elsewhere on the board

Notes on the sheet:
D-BS-8S-0-19
Program Counter
